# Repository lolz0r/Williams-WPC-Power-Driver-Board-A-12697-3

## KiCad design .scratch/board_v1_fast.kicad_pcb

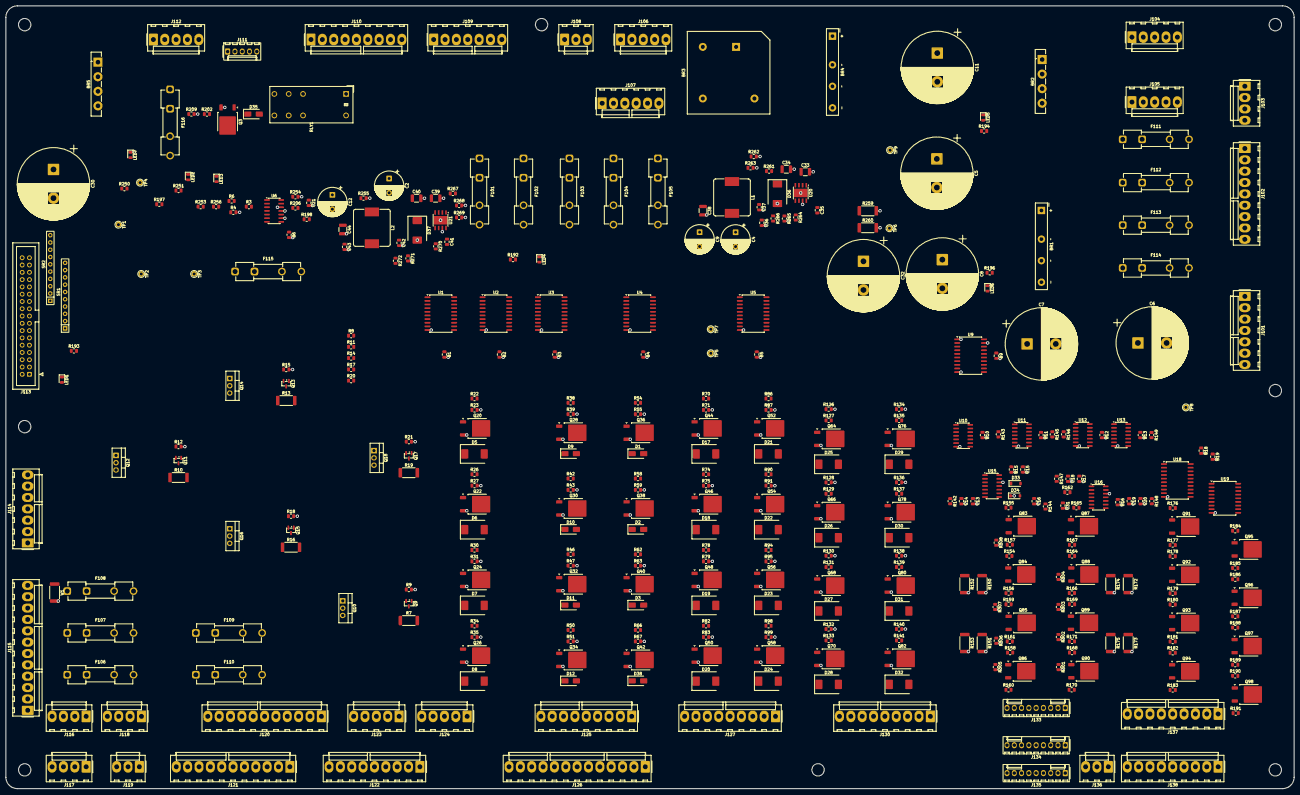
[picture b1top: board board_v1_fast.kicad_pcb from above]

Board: 4 copper layers, 449.2 x 272.9 mm, 398 parts (0 on the bottom side), 292 nets.

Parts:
B1, B2, B3, B4, B5, B6, B9, B10, B11, B12, B13, B15, B16, B18, B19: 100nF; C_0805_2012Metric
BR1, BR4: GBJ1510; Diode_Bridge_GBJ
BR2, BR5: GBU8J; Diode_Bridge_Vishay_GBU
BR3: GBPC3510; Diode_Bridge_28.6x28.6x7.3mm_P18.0mm_P11.6mm
C2, C4, C9, C12: 330uF; CP_Radial_D10.0mm_P5.00mm
C5, C6, C7, C11, C30: 10000uF 25V; CP_Radial_D25.0mm_P10.00mm_SnapIn
C8, C32: 2200uF 100V; CP_Radial_D25.0mm_P10.00mm_SnapIn
C13, C14, C15, C16, C17, C18, C19, C20, C31, C35, C41, C42: 100nF; C_0805_2012Metric
C21: 10nF; C_0805_2012Metric
C33, C34, C38, C39, C40, C44: 10uF; C_1210_3225Metric
C36: 33nF; C_0805_2012Metric
C37: 470pF; C_0805_2012Metric
C43: 390pF; C_0805_2012Metric
D1, D2, D3, D9, D10, D11, D12, D38: S1M-13-F; D_SMA
D5, D6, D7, D8, D17, D18, D19, D20, D21, D22, D23, D24, D25, D26, D27, D28, D29, D30, D31, D32: S3M-13-F; D_SMC
D33, D34: 1N4148W; D_SOD-123
D35: S1M (DNP); D_SMA
D36, D37: B560C; D_SMC
F101, F102: no fuse (clips only); Fuseholder_Clip-5x20mm_Keystone_3517_Inline_P23.11x6.76mm_D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
F103, F104, F105, F116: 3A S.B.; Fuseholder_Clip-5x20mm_Keystone_3517_Inline_P23.11x6.76mm_D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
F106, F107, F108, F109, F110, F111, F113: 5A S.B.; Fuseholder_Clip-5x20mm_Keystone_3517_Inline_P23.11x6.76mm_D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
F112: 7A S.B.; Fuseholder_Clip-5x20mm_Keystone_3517_Inline_P23.11x6.76mm_D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
F114: 8A; Fuseholder_Clip-5x20mm_Keystone_3517_Inline_P23.11x6.76mm_D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
F115: 3/4A S.B.; Fuseholder_Clip-5x20mm_Keystone_3517_Inline_P23.11x6.76mm_D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
H1, H2, H3, H4, H5, H6, H7, H8: M4; MountingHole_4.3mm_M4
J101: J101 xformer 9VAC (Red) / 13VAC (Blu-Wht); Molex_KK-396_A-41791-0007_1x07_P3.96mm_Vertical
J102: J102 xformer 16VAC (Wht-Red) / solenoid ~51VAC (B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; Molex_KK-396_A-41791-0009_1x09_P3.96mm_Vertical
J103: J103 ground to 8-driver board; Molex_KK-396_A-41791-0004_1x04_P3.96mm_Vertical
J104: J104 solenoid AC (~51 VAC, unfused) to Fliptronic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; Molex_KK-396_A-41791-0005_1x05_P3.96mm_Vertical
J105: J105 flipper AC (relay switched, N/C on Fliptroni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; Molex_KK-396_A-41791-0005_1x05_P3.96mm_Vertical
J106: J106 +20V to backbox flashlamps; Molex_KK-396_A-41791-0005_1x05_P3.96mm_Vertical
J107: J107 +50V (F103/F104/F105) and +20V to playfield; Molex_KK-396_A-41791-0006_1x06_P3.96mm_Vertical
J108: J108 spare (N/C); Molex_KK-396_A-41791-0003_1x03_P3.96mm_Vertical
J109: J109 spare (N/C); Molex_KK-396_A-41791-0007_1x07_P3.96mm_Vertical
J110: J110 spare (N/C); Molex_KK-396_A-41791-0009_1x09_P3.96mm_Vertical
J111: J111 G.I. latch spare bits T5-T7 (GPIO as on the 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; Molex_KK-254_AE-6410-05A_1x05_P2.54mm_Vertical
J112: J112 xformer 9.8VAC (Wht-Grn); Molex_KK-396_A-41791-0005_1x05_P3.96mm_Vertical
J113: 34-pin ribbon to CPU J211; IDC-Header_2x17_P2.54mm_Vertical
J114: J114 +12V/+5V/GND to CPU J210, Fliptronic J904, 8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; Molex_KK-396_A-41791-0007_1x07_P3.96mm_Vertical
J115: J115 G.I. 6.3VAC from transformer: 2-6 string hot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; Molex_KK-396_A-41791-0012_1x12_P3.96mm_Vertical
J116: J116 +12V power (unregulated) / GND / +5V to coin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; Molex_KK-396_A-41791-0004_1x04_P3.96mm_Vertical
J117: J117 +12V power (unregulated) / GND / +5V to DMD 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; Molex_KK-396_A-41791-0004_1x04_P3.96mm_Vertical
J118: J118 +12V power (unregulated) / GND / +5V to play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; Molex_KK-396_A-41791-0004_1x04_P3.96mm_Vertical
J119: J119 G.I. coin door (string 5); Molex_KK-396_A-41791-0003_1x03_P3.96mm_Vertical
J120: J120 G.I. backbox (strings 2,3); Molex_KK-396_A-41791-0011_1x11_P3.96mm_Vertical
J121: J121 G.I. playfield (strings 1,4,5); Molex_KK-396_A-41791-0011_1x11_P3.96mm_Vertical
J122: J122 Sol 25-28 drive + tie-back (playfield); Molex_KK-396_A-41791-0009_1x09_P3.96mm_Vertical
J123: J123 spare (N/C); Molex_KK-396_A-41791-0005_1x05_P3.96mm_Vertical
J124: J124 Sol 25-28 drive (backbox); Molex_KK-396_A-41791-0005_1x05_P3.96mm_Vertical
J125: J125 Sol 17-24 drive (backbox flashers); Molex_KK-396_A-41791-0009_1x09_P3.96mm_Vertical
J126: J126 Sol 17-24 drive (playfield flashers); Molex_KK-396_A-41791-0013_1x13_P3.96mm_Vertical
J127: J127 Sol 9-16 drive (playfield); Molex_KK-396_A-41791-0009_1x09_P3.96mm_Vertical
J130: J130 Sol 1-8 drive (playfield); Molex_KK-396_A-41791-0009_1x09_P3.96mm_Vertical
J133: J133 lamp rows (cabinet); Molex_KK-254_AE-6410-09A_1x09_P2.54mm_Vertical
J134: J134 lamp rows (spare); Molex_KK-254_AE-6410-09A_1x09_P2.54mm_Vertical
J135: J135 lamp rows (playfield); Molex_KK-254_AE-6410-09A_1x09_P2.54mm_Vertical
J136: J136 lamp column 8 (cabinet); Molex_KK-396_A-41791-0003_1x03_P3.96mm_Vertical
J137: J137 lamp columns (playfield); Molex_KK-396_A-41791-0009_1x09_P3.96mm_Vertical
J138: J138 lamp columns (backbox); Molex_KK-396_A-41791-0009_1x09_P3.96mm_Vertical
L1, L2: 10uH; L_Bourns_SRP1245A
LED1, LED2, LED4, LED5, LED6, LED7: LED red; LED_0805_2012Metric
LED3: LED red (ZC); LED_0805_2012Metric
Q3: IRLR3110ZTRPBF (DNP); TO-252-2
Q9, Q11, Q13, Q15, Q17: MMBT4401; SOT-23
Q10, Q12, Q14, Q16, Q18: BTA16-600CRG; TO-220-3_Vertical
Q20, Q22, Q24, Q26, Q28, Q30, Q32, Q34, Q36, Q38, Q40, Q42, Q44, Q46, Q48, Q50, Q52, Q54, Q56, Q58, Q64, Q66, Q68, Q70, Q76, Q78, Q80, Q82: IRLR3110ZTRPBF; TO-252-2
Q83, Q84, Q85, Q86, Q87, Q88, Q89, Q90: IRLR024NTRPBF; TO-252-2
Q91, Q92, Q93, Q94, Q95, Q96, Q97, Q98: IRFR5305TRPBF; TO-252-2
R3, R4, R6, R9, R12, R15, R18, R21, R23, R27, R31, R35, R39, R43, R47, R51, R55, R59, R63, R67, R71, R75, R79, R83, R87, R91, R95, R99, R126, R128, R130, R132, R134, R136, R138, R140, R142, R143, R144, R145, R146, R147, R148, R149, R197, R198, R301, R302, R303, R304, R305, R306, R307, R308: 10K; R_0805_2012Metric
R7, R10, R13, R16, R19: 27; R_2512_6332Metric
R8, R11, R14, R17, R20: 470; R_0805_2012Metric
R22, R26, R30, R34, R38, R42, R46, R50, R54, R58, R62, R66, R70, R74, R78, R82, R86, R90, R94, R98, R127, R129, R131, R133, R135, R137, R139, R141, R155, R157, R159, R161, R165, R167, R169, R171: 100; R_0805_2012Metric
R150, R151, R152, R153, R172, R173, R174, R175: 0.22R; R_2512_6332Metric
R154, R156, R158, R160, R162, R164, R166, R168, R170, R177, R179, R181, R183, R185, R187, R189, R191, R193: 1K; R_0805_2012Metric
R176, R178, R180, R182, R184, R186, R188, R190, R194, R196, R250, R251, R253, R254, R255, R256: 1.5K; R_0805_2012Metric
R192: 270; R_0805_2012Metric
R202: 100 (DNP); R_0805_2012Metric
R206: 27K; R_0805_2012Metric
R209: 10K (DNP); R_0805_2012Metric
R259, R260: 15K; R_2512_6332Metric
R261: 118K; R_0805_2012Metric
R262: 29.4K; R_0805_2012Metric
R263, R269: 240K; R_0805_2012Metric
R264: 10.5K; R_0805_2012Metric
R265, R271: 2K; R_0805_2012Metric
R266: 33.2K; R_0805_2012Metric
R267: 130K; R_0805_2012Metric
R268: 20K; R_0805_2012Metric
R270: 28K; R_0805_2012Metric
R272: 42.2K; R_0805_2012Metric
RLY1: G2RL-2 12V (DNP); Relay_DPDT_Omron_G2RL-2
SR1, SR2: 9x4.7K SIP; R_Array_SIP10
TP1: TP1 +12VU; TestPoint_THTPad_D2.0mm_Drill1.0mm
TP2: TP2 +5V; TestPoint_THTPad_D2.0mm_Drill1.0mm
TP3: TP3 +12V; TestPoint_THTPad_D2.0mm_Drill1.0mm
TP4: TP4 ZC; TestPoint_THTPad_D2.0mm_Drill1.0mm
TP5: TP5 GND; TestPoint_THTPad_D2.0mm_Drill1.0mm
TP6: TP6 +50V; TestPoint_THTPad_D2.0mm_Drill1.0mm
TP7: TP7 +20V; TestPoint_THTPad_D2.0mm_Drill1.0mm
TP8: TP8 +18V; TestPoint_THTPad_D2.0mm_Drill1.0mm
TP9: TP9 +5V_RAW; TestPoint_THTPad_D2.0mm_Drill1.0mm
U1, U2, U3, U4, U5, U18: 74HCT574; SOIC-20W_7.5x12.8mm_P1.27mm
U6, U15, U16: LM339DR; SOIC-14_3.9x8.7mm_P1.27mm
U9: 74HCT240; SOIC-20W_7.5x12.8mm_P1.27mm
U10, U11, U12, U13: 74HCT74; SOIC-14_3.9x8.7mm_P1.27mm
U19: TBD62083AFWG; SOIC-18W_7.5x11.6mm_P1.27mm
U20, U21: TPS54360BDDAR; Texas_HSOP-8-1EP_3.9x4.9mm_P1.27mm
W1: 0R; R_2512_6332Metric

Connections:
+5V: B1.1, B2.1, B3.1, B4.1, B5.1, B6.1, B9.1, B10.1, B11.1, B12.1, B13.1, B15.1, B16.1, B18.1, B19.1, C4.1, C9.1, C38.1, J114.3, J114.4, J116.4, J117.4, J118.4, L1.2, LED3.2, Q9.3, Q11.3, Q13.3, Q15.3, Q17.3, R3.1, R142.1, R143.1, R144.1, R145.1, R146.1, R147.1, R148.1, R149.1, R162.1, R192.1, R206.1, R256.1, R264.1, SR1.1, SR2.1, TP2.1, U1.20, U2.20, U3.20, U4.20, U5.20, U6.3, U6.8, U6.10, U9.20, U10.4, U10.10, U10.14, U11.4, U11.10, U11.14, U12.4, U12.10, U12.14, U13.4, U13.10, U13.14, U15.3, U16.3, U18.20
+12V: C2.1, C12.1, C44.1, D35.1, F115.1, L2.2, R193.1, R270.1, RLY1.A1, TP3.1
+12VU: BR5.1, C30.1, J116.2, J117.2, J118.2, R250.1, TP1.1
+12V_F: F115.2, J114.1, J114.2, R251.1
+18V: BR1.1, C6.1, C7.1, C39.1, C40.1, Q91.3, Q92.3, Q93.3, Q94.3, Q95.3, Q96.3, Q97.3, Q98.3, R176.1, R178.1, R180.1, R182.1, R184.1, R186.1, R188.1, R190.1, R196.1, R267.1, TP8.1, U19.10, U21.2
+20V: BR4.1, C11.1, D1.1, D2.1, D3.1, D9.1, D10.1, D11.1, D12.1, D38.1, J106.5, J107.6, R194.1, TP7.1
+50V: BR3.1, C8.1, C32.1, D17.1, D18.1, D19.1, D20.1, D21.1, D22.1, D23.1, D24.1, D25.1, D26.1, D27.1, D28.1, D29.1, D30.1, D31.1, D32.1, F103.1, F104.1, F105.1, R259.1, R260.1, TP6.1
+50V_F103: F103.2, J107.1
+50V_F104: F104.2, J107.2
+50V_F105: F105.2, J107.3
/CPU_Interface/BLK_REF: R3.2, R4.1, U6.7
/CPU_Interface/ZC_REF: R206.2, R255.1, U6.5
/CPU_Interface/ZC_SAMPLE: C21.1, R197.2, R198.2, R254.1, U6.4
/GI_Triacs/GI1_G: Q18.3, R19.2
/GI_Triacs/GI2_G: Q10.3, R7.2
/GI_Triacs/GI3_G: Q14.3, R13.2
/GI_Triacs/GI4_G: Q16.3, R16.2
/GI_Triacs/GI5_G: Q12.3, R10.2
/GI_Triacs/RLY_COIL: D35.2, Q3.2, RLY1.A2
/Lamp_Rows/ROW1_E: Q90.3, R170.1, R175.1
/Lamp_Rows/ROW1_Q: R171.1, U13.9
/Lamp_Rows/ROW1_S: C20.1, R170.2, U16.8
/Lamp_Rows/ROW2_E: Q89.3, R168.1, R173.1
/Lamp_Rows/ROW2_Q: R169.1, U13.5
/Lamp_Rows/ROW2_S: C19.1, R168.2, U16.10
/Lamp_Rows/ROW3_E: Q88.3, R166.1, R174.1
/Lamp_Rows/ROW3_Q: R167.1, U12.9
/Lamp_Rows/ROW3_S: C18.1, R166.2, U16.6
/Lamp_Rows/ROW4_E: Q87.3, R164.1, R172.1
/Lamp_Rows/ROW4_Q: R165.1, U12.5
/Lamp_Rows/ROW4_S: C17.1, R164.2, U16.4
/Lamp_Rows/ROW5_E: Q86.3, R153.1, R160.1
/Lamp_Rows/ROW5_Q: R161.1, U11.9
/Lamp_Rows/ROW5_S: C16.1, R160.2, U15.8
/Lamp_Rows/ROW6_E: Q85.3, R151.1, R158.1
/Lamp_Rows/ROW6_Q: R159.1, U11.5
/Lamp_Rows/ROW6_S: C15.1, R158.2, U15.10
/Lamp_Rows/ROW7_E: Q84.3, R152.1, R156.1
/Lamp_Rows/ROW7_Q: R157.1, U10.9
/Lamp_Rows/ROW7_S: C14.1, R156.2, U15.6
/Lamp_Rows/ROW8_E: Q83.3, R150.1, R154.1
/Lamp_Rows/ROW8_Q: R155.1, U10.5
/Lamp_Rows/ROW8_S: C13.1, R154.2, U15.4
/Power_Supply/+5V_RAW: BR2.1, C5.1, C33.1, C34.1, R261.1, TP9.1, U20.2
/Power_Supply/AC9_A_F: BR2.3, F113.2
/Power_Supply/AC13_A_F: BR1.3, F114.2
/Power_Supply/AC16_A_F: BR4.3, F111.2
/Power_Supply/AC98_A_F: BR5.3, F116.2
/Power_Supply/ACSOL_A_F: BR3.3, F112.2
/Power_Supply/U20_BOOT: C35.1, U20.1
/Power_Supply/U20_CC: C36.1, R266.2
/Power_Supply/U20_COMP: C37.1, R266.1, U20.6
/Power_Supply/U20_EN: R261.2, R262.1, U20.3
/Power_Supply/U20_FB: R264.2, R265.1, U20.5
/Power_Supply/U20_RT: R263.1, U20.4
/Power_Supply/U20_SW: C35.2, D36.1, L1.1, U20.8
/Power_Supply/U21_BOOT: C41.1, U21.1
/Power_Supply/U21_CC: C42.1, R272.2
/Power_Supply/U21_COMP: C43.1, R272.1, U21.6
/Power_Supply/U21_EN: R267.2, R268.1, U21.3
/Power_Supply/U21_FB: R270.2, R271.1, U21.5
/Power_Supply/U21_RT: R269.1, U21.4
/Power_Supply/U21_SW: C41.2, D37.1, L2.1, U21.8
/Sol_Flashers/S17_G: Q42.1, R66.2, R67.1
/Sol_Flashers/S18_G: Q40.1, R62.2, R63.1
/Sol_Flashers/S19_G: Q38.1, R58.2, R59.1
/Sol_Flashers/S20_G: Q36.1, R54.2, R55.1
/Sol_Flashers/S21_G: Q28.1, R38.2, R39.1
/Sol_Flashers/S22_G: Q30.1, R42.2, R43.1
/Sol_Flashers/S23_G: Q34.1, R50.2, R51.1
/Sol_Flashers/S24_G: Q32.1, R46.2, R47.1
/Sol_GeneralPurpose/S25_G: Q26.1, R34.2, R35.1
/Sol_GeneralPurpose/S26_G: Q24.1, R30.2, R31.1
/Sol_GeneralPurpose/S27_G: Q22.1, R26.2, R27.1
/Sol_GeneralPurpose/S28_G: Q20.1, R22.2, R23.1
/Sol_HighPower/S01_G: Q82.1, R140.1, R141.2
/Sol_HighPower/S02_G: Q80.1, R138.1, R139.2
/Sol_HighPower/S03_G: Q78.1, R136.1, R137.2
/Sol_HighPower/S04_G: Q76.1, R134.1, R135.2
/Sol_HighPower/S05_G: Q64.1, R126.1, R127.2
/Sol_HighPower/S06_G: Q66.1, R128.1, R129.2
/Sol_HighPower/S07_G: Q68.1, R130.1, R131.2
/Sol_HighPower/S08_G: Q70.1, R132.1, R133.2
/Sol_LowPower/S09_G: Q58.1, R98.2, R99.1
/Sol_LowPower/S10_G: Q56.1, R94.2, R95.1
/Sol_LowPower/S11_G: Q54.1, R90.2, R91.1
/Sol_LowPower/S12_G: Q52.1, R86.2, R87.1
/Sol_LowPower/S13_G: Q50.1, R82.2, R83.1
/Sol_LowPower/S14_G: Q48.1, R78.2, R79.1
/Sol_LowPower/S15_G: Q46.1, R74.2, R75.1
/Sol_LowPower/S16_G: Q44.1, R70.2, R71.1
AC9_A: F113.1, J101.1
AC9_B: BR2.2, J101.2
AC13_A: F114.1, J101.4, J101.5
AC13_B: BR1.4, J101.6, J101.7
AC16_A: F111.1, J102.1, J102.2
AC16_B: BR4.4, J102.3, J102.4
AC98_A: F116.1, J112.1, J112.2, R197.1
AC98_B: BR5.2, J112.3, J112.5, R198.1
ACSOL_A: F112.1, J102.5, J102.6, J104.2, RLY1.11, RLY1.21
ACSOL_B: BR3.4, J102.8, J102.9, J104.1, J105.4, J105.5
BLANKING: J113.31, R6.1, SR1.9, U1.1, U2.1, U3.1, U4.1, U5.1, U18.1
CLK_GI: J113.13, SR1.8, U1.11
CLK_LAMP_COL: J113.8, SR1.2, U18.11
CLK_LAMP_ROW: J113.7, SR1.3, U10.3, U10.11, U11.3, U11.11, U12.3, U12.11, U13.3, U13.11
CLK_SOL_FLASH: J113.9, SR1.6, U3.11
CLK_SOL_GEN: J113.12, SR1.4, U2.11
CLK_SOL_HIGH: J113.10, SR1.5, U5.11
CLK_SOL_LOW: J113.11, SR1.7, U4.11
COL1: J137.1, J138.1, Q98.2
COL2: J137.2, J138.2, Q97.2
COL3: J137.3, J138.3, Q96.2
COL4: J137.4, J138.4, Q95.2
COL5: J137.5, J138.5, Q94.2
COL6: J137.6, J138.6, Q93.2
COL7: J137.7, J138.7, Q92.2
COL8: J136.3, J137.9, J138.9, Q91.2
COLB1: R191.1, U19.18
COLB2: R189.1, U19.17
COLB3: R187.1, U19.16
COLB4: R185.1, U19.15
COLB5: R183.1, U19.14
COLB6: R181.1, U19.13
COLB7: R179.1, U19.12
COLB8: R177.1, U19.11
COLDRV1: U18.19, U19.1
COLDRV2: U18.18, U19.2
COLDRV3: U18.17, U19.3
COLDRV4: U18.16, U19.4
COLDRV5: U18.15, U19.5
COLDRV6: U18.14, U19.6
COLDRV7: U18.13, U19.7
COLDRV8: U18.12, U19.8
D0: U1.2, U2.2, U3.2, U4.2, U5.2, U9.18, U13.12, U18.2
D0_N: J113.29, SR2.2, U9.2
D1: U1.3, U2.3, U3.3, U4.3, U5.3, U9.16, U13.2, U18.3
D1_N: J113.27, SR2.3, U9.4
D2: U1.4, U2.4, U3.4, U4.4, U5.4, U9.14, U12.12, U18.4
D2_N: J113.25, SR2.4, U9.6
D3: U1.5, U2.5, U3.5, U4.5, U5.5, U9.12, U12.2, U18.5
D3_N: J113.23, SR2.5, U9.8
D4: U1.6, U2.6, U3.6, U4.6, U5.6, U9.3, U11.12, U18.6
D4_N: J113.21, SR2.6, U9.17
D5: U1.7, U2.7, U3.7, U4.7, U5.7, U9.5, U11.2, U18.7
D5_N: J113.19, SR2.7, U9.15
D6: U1.8, U2.8, U3.8, U4.8, U5.8, U9.7, U10.12, U18.8
D6_N: J113.17, SR2.8, U9.13
D7: U1.9, U2.9, U3.9, U4.9, U5.9, U9.9, U10.2, U18.9
D7_N: J113.15, SR2.9, U9.11
FLIP_L_AC: F101.1, J105.1
FLIP_RLY_L: J111.3, R202.1, U1.12
FLIP_R_AC: F102.1, J105.2
GI1_IN: F110.1, J115.2
GI1_L: R20.1, U1.19
GI1_OUT: F110.2, J121.7
GI1_RET: J121.1, Q18.2
GI2_IN: F109.1, J115.4
GI2_L: R8.1, U1.18
GI2_OUT: F109.2, J120.8
GI2_RET: J120.2, Q10.2
GI3_IN: F108.1, J115.5
GI3_L: R14.1, U1.17
GI3_OUT: F108.2, J120.9
GI3_RET: J120.3, Q14.2
GI4_IN: F107.1, J115.3
GI4_L: R17.1, U1.16
GI4_OUT: F107.2, J121.10
GI4_RET: J121.5, Q16.2
GI5_IN: F106.1, J115.6
GI5_L: R11.1, U1.15
GI5_OUT: F106.2, J119.1, J121.11
GI5_RET: J119.3, J121.6, Q12.2
GI_BIT5: J111.1, U1.14
GI_BIT6: J111.2, U1.13
GI_RET: J115.7, J115.8, J115.10, J115.11, J115.12, Q10.1, Q12.1, Q14.1, Q16.1, Q18.1, W1.1
GND: B1.2, B2.2, B3.2, B4.2, B5.2, B6.2, B9.2, B10.2, B11.2, B12.2, B13.2, B15.2, B16.2, B18.2, B19.2, BR1.2, BR2.4, BR3.2, BR4.2, BR5.4, C2.2, C4.2, C5.2, C6.2, C7.2, C8.2, C9.2, C11.2, C12.2, C13.2, C14.2, C15.2, C16.2, C17.2, C18.2, C19.2, C20.2, C21.2, C30.2, C31.2, C32.2, C33.2, C34.2, C36.2, C37.2, C38.2, C39.2, C40.2, C42.2, C43.2, C44.2, D34.1, D36.2, D37.2, J103.1, J103.2, J111.5, J113.4, J113.6, J113.14, J113.16, J113.18, J113.20, J113.22, J113.24, J113.26, J113.28, J113.30, J114.5, J114.7, J115.1, J116.3, J117.3, J118.3, LED1.1, LED2.1, LED4.1, LED5.1, LED6.1, LED7.1, Q3.3, Q20.3, Q22.3, Q24.3, Q26.3, Q28.3, Q30.3, Q32.3, Q34.3, Q36.3, Q38.3, Q40.3, Q42.3, Q44.3, Q46.3, Q48.3, Q50.3, Q52.3, Q54.3, Q56.3, Q58.3, Q64.3, Q66.3, Q68.3, Q70.3, Q76.3, Q78.3, Q80.3, Q82.3, R4.2, R9.2, R12.2, R15.2, R18.2, R21.2, R23.2, R27.2, R31.2, R35.2, R39.2, R43.2, R47.2, R51.2, R55.2, R59.2, R63.2, R67.2, R71.2, R75.2, R79.2, R83.2, R87.2, R91.2, R95.2, R99.2, R126.2, R128.2, R130.2, R132.2, R134.2, R136.2, R138.2, R140.2, R150.2, R151.2, R152.2, R153.2, R172.2, R173.2, R174.2, R175.2, R209.2, R254.2, R255.2, R259.2, R260.2, R262.2, R263.2, R265.2, R268.2, R269.2, R271.2, R301.2, R302.2, R303.2, R304.2, R305.2, R306.2, R307.2, R308.2, TP5.1, U1.10, U2.10, U3.10, U4.10, U5.10, U6.9, U6.11, U6.12, U9.1, U9.10, U9.19, U10.7, U11.7, U12.7, U13.7, U15.12, U16.12, U18.10, U19.9, U20.7, U20.9, U21.7, U21.9, W1.2
unnamed: D33.1, D34.2
unnamed: F101.2, RLY1.14
unnamed: F102.2, RLY1.24
unnamed: LED1.2, R193.2
unnamed: LED2.2, R251.2
unnamed: LED3.1, R253.2
unnamed: LED4.2, R192.2
unnamed: LED5.2, R194.2
unnamed: LED6.2, R196.2
unnamed: LED7.2, R250.2
unnamed: Q3.1, R202.2, R209.1
unnamed: Q9.1, R8.2, R9.1
unnamed: Q9.2, R7.1
unnamed: Q11.1, R11.2, R12.1
unnamed: Q11.2, R10.1
unnamed: Q13.1, R14.2, R15.1
unnamed: Q13.2, R13.1
unnamed: Q15.1, R17.2, R18.1
unnamed: Q15.2, R16.1
unnamed: Q17.1, R20.2, R21.1
unnamed: Q17.2, R19.1
unnamed: Q83.1, R155.2, R308.1
unnamed: Q84.1, R157.2, R307.1
unnamed: Q85.1, R159.2, R306.1
unnamed: Q86.1, R161.2, R305.1
unnamed: Q87.1, R165.2, R304.1
unnamed: Q88.1, R167.2, R303.1
unnamed: Q89.1, R169.2, R302.1
unnamed: Q90.1, R171.2, R301.1
unnamed: Q91.1, R176.2, R177.2
unnamed: Q92.1, R178.2, R179.2
unnamed: Q93.1, R180.2, R181.2
unnamed: Q94.1, R182.2, R183.2
unnamed: Q95.1, R184.2, R185.2
unnamed: Q96.1, R186.2, R187.2
unnamed: Q97.1, R188.2, R189.2
unnamed: Q98.1, R190.2, R191.2
unnamed: R6.2, U6.6
REF_1V4: C31.1, D33.2, R162.2, U6.1, U15.5, U15.7, U15.9, U15.11, U16.5, U16.7, U16.9, U16.11
ROW1: J133.1, J134.1, J135.1, Q90.2
ROW2: J133.2, J134.2, J135.2, Q89.2
ROW3: J133.4, J134.4, J135.4, Q88.2
ROW4: J133.5, J134.5, J135.5, Q87.2
ROW5: J133.6, J134.6, J135.6, Q86.2
ROW6: J133.7, J134.7, J135.7, Q85.2
ROW7: J133.8, J134.8, J135.8, Q84.2
ROW8: J133.9, J134.9, J135.9, Q83.2
ROWCLR1: R149.2, U13.13, U16.14
ROWCLR2: R148.2, U13.1, U16.13
ROWCLR3: R147.2, U12.13, U16.1
ROWCLR4: R146.2, U12.1, U16.2
ROWCLR5: R145.2, U11.13, U15.14
ROWCLR6: R144.2, U11.1, U15.13
ROWCLR7: R143.2, U10.13, U15.1
ROWCLR8: R142.2, U10.1, U15.2
SOL01: D32.2, J130.1, Q82.2
SOL01_L: R141.1, U5.19
SOL02: D31.2, J130.2, Q80.2
SOL02_L: R139.1, U5.18
SOL03: D30.2, J130.4, Q78.2
SOL03_L: R137.1, U5.17
SOL04: D29.2, J130.5, Q76.2
SOL04_L: R135.1, U5.16
SOL05: D25.2, J130.6, Q64.2
SOL05_L: R127.1, U5.15
SOL06: D26.2, J130.7, Q66.2
SOL06_L: R129.1, U5.14
SOL07: D27.2, J130.8, Q68.2
SOL07_L: R131.1, U5.13
SOL08: D28.2, J130.9, Q70.2
SOL08_L: R133.1, U5.12
SOL09: D24.2, J127.1, Q58.2
SOL09_L: R98.1, U4.19
SOL10: D23.2, J127.3, Q56.2
SOL10_L: R94.1, U4.18
SOL11: D22.2, J127.4, Q54.2
SOL11_L: R90.1, U4.17
SOL12: D21.2, J127.5, Q52.2
SOL12_L: R86.1, U4.16
SOL13: D20.2, J127.6, Q50.2
SOL13_L: R82.1, U4.15
SOL14: D19.2, J127.7, Q48.2
SOL14_L: R78.1, U4.14
SOL15: D18.2, J127.8, Q46.2
SOL15_L: R74.1, U4.13
SOL16: D17.2, J127.9, Q44.2
SOL16_L: R70.1, U4.12
SOL17: D38.2, J125.1, J126.1, Q42.2
SOL17_L: R66.1, U3.19
SOL18: D3.2, J125.2, J126.2, Q40.2
SOL18_L: R62.1, U3.18
SOL19: D2.2, J125.3, J126.3, Q38.2
SOL19_L: R58.1, U3.17
SOL20: D1.2, J125.4, J126.4, Q36.2
SOL20_L: R54.1, U3.16
SOL21: D9.2, J125.6, J126.5, Q28.2
SOL21_L: R38.1, U3.15
SOL22: D10.2, J125.7, J126.6, Q30.2
SOL22_L: R42.1, U3.14
SOL23: D12.2, J125.8, J126.7, Q34.2
SOL23_L: R50.1, U3.13
SOL24: D11.2, J125.9, J126.8, Q32.2
SOL24_L: R46.1, U3.12
SOL25: D8.2, J122.1, J124.1, Q26.2
SOL25_L: R34.1, U2.19
SOL25_TB: D8.1, J122.5
SOL26: D7.2, J122.2, J124.2, Q24.2
SOL26_L: R30.1, U2.18
SOL26_TB: D7.1, J122.6
SOL27: D6.2, J122.3, J124.3, Q22.2
SOL27_L: R26.1, U2.17
SOL27_TB: D6.1, J122.8
SOL28: D5.2, J122.4, J124.5, Q20.2
SOL28_L: R22.1, U2.16
SOL28_TB: D5.1, J122.9
ZERO_CROSS: J113.34, R253.1, R256.2, TP4.1, U6.2
